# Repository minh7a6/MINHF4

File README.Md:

MINHF4 Hardware Design File. This board is designed using EAGLE 9.2.2

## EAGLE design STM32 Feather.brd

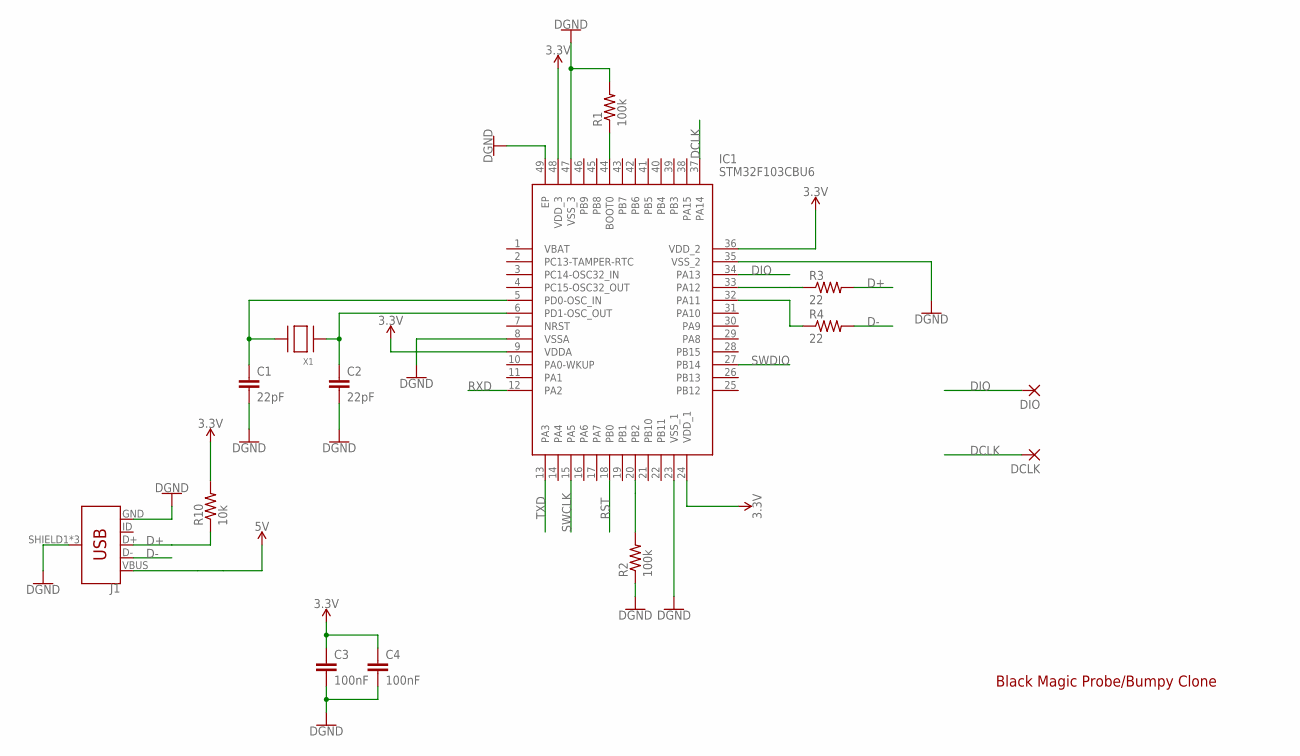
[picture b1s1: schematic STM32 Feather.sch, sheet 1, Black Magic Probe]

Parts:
C1, C2: 22pF; C0603
C3, C4: 100nF; C0603
DCLK: SMD2; SMD1,27-2,54
DIO: SMD2; SMD1,27-2,54
IC1: STM32F103CBU6; QFN50P700X700X65-49N
J1: USB_MICRO-B_FEMALE-SMT; USB-B-MICRO-SMD
R1, R2: 100k; R0603
R3, R4: 22; R0603
R10: 10k; R0603
X1: XTALNX5032; NX5032

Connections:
3.3V: C3.1, C4.1, IC1.9 (VDDA), IC1.24 (VDD_1), IC1.36 (VDD_2), IC1.48 (VDD_3), R10.2; also elsewhere on the board
5V: J1.VBUS; also elsewhere on the board
D+: J1.D+, R3.2, R10.1
D-: J1.D-, R4.2
DCLK: DCLK.1, IC1.37 (PA14)
DIO: DIO.1, IC1.34 (PA13)
GND: C1.2, C2.2, C3.2, C4.2, IC1.8 (VSSA), IC1.23 (VSS_1), IC1.35 (VSS_2), IC1.47 (VSS_3), IC1.49 (EP), J1.GND, J1.SHIELD1 (SHIELD), J1.SHIELD2 (SHIELD), J1.SHIELD3 (SHIELD), R1.2, R2.1; also elsewhere on the board
unnamed: C1.1, IC1.5 (PD0-OSC_IN), X1.P$2
unnamed: C2.1, IC1.6 (PD1-OSC_OUT), X1.P$1
unnamed: IC1.44 (BOOT0), R1.1
unnamed: IC1.20 (PB2), R2.2
unnamed: IC1.33 (PA12), R3.1
unnamed: IC1.32 (PA11), R4.1
RST: IC1.18 (PB0); also elsewhere on the board
RXD: IC1.12 (PA2); also elsewhere on the board
SWCLK: IC1.15 (PA5); also elsewhere on the board
SWDIO: IC1.27 (PB14); also elsewhere on the board
TXD: IC1.13 (PA3); also elsewhere on the board

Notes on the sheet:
Black Magic Probe/Bumpy Clone

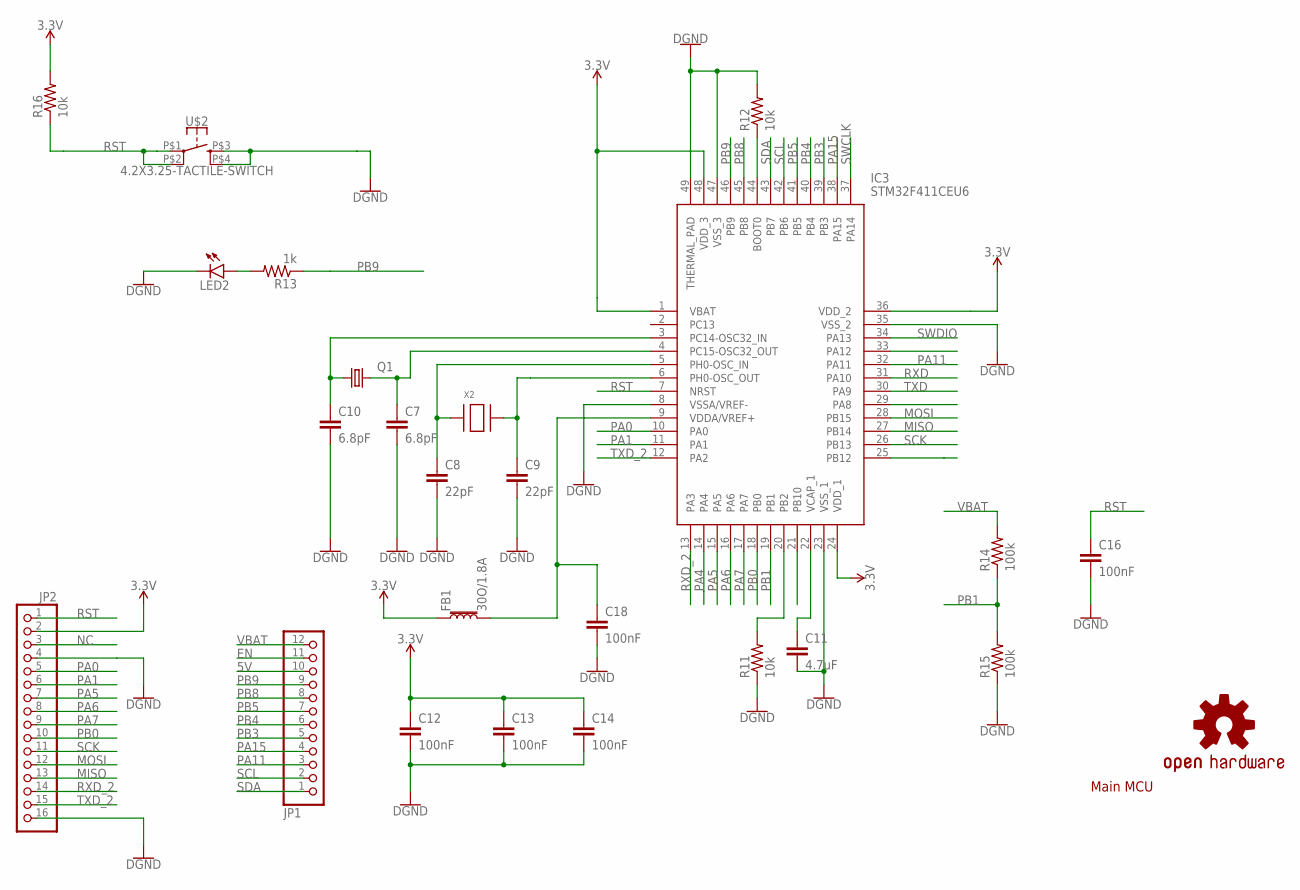
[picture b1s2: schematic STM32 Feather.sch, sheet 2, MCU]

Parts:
C7, C10: 6.8pF; C0603
C8, C9: 22pF; C0603
C11: 4.7uF; C0603
C12, C13, C14, C16, C18: 100nF; C0603
FB1: 30O/1.8A; 0603
IC3: STM32F411CEU6; QFN50P700X700X60-49N
JP1: PINHD-1X12; 1X12
JP2: PINHD-1X16; 1X16
LED2: LEDCHIP-LED0603; CHIP-LED0603
LOGO1: OSHW-LOGOMINI; OSHW-LOGO-MINI
Q1: KX-327-NHF; 3.2X1.5
R11, R12, R16: 10k; R0603
R13: 1k; R0603
R14, R15: 100k; R0603
U$2: 4.2X3.25-TACTILE-SWITCH; 4.2X3.25
X2: XTALNX5032; NX5032

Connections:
3.3V: C12.1, C13.1, C14.1, FB1.1, IC3.1 (VBAT), IC3.24 (VDD_1), IC3.36 (VDD_2), IC3.48 (VDD_3), JP2.2, R16.2; also elsewhere on the board
5V: JP1.10; also elsewhere on the board
EN: JP1.11
GND: C7.2, C8.2, C9.2, C10.2, C11.2, C12.2, C13.2, C14.2, C16.2, C18.2, IC3.8 (VSSA/VREF-), IC3.23 (VSS_1), IC3.35 (VSS_2), IC3.47 (VSS_3), IC3.49 (THERMAL_PAD), JP2.4, JP2.16, LED2.C, R11.1, R12.2, R15.1, U$2.P$3 (3), U$2.P$4 (4); also elsewhere on the board
MISO: IC3.27 (PB14), JP2.13
MOSI: IC3.28 (PB15), JP2.12
unnamed: LED2.A, R13.2
unnamed: C7.1, IC3.4 (PC15-OSC32_OUT), Q1.2
unnamed: C10.1, IC3.3 (PC14-OSC32_IN), Q1.1
unnamed: C18.1, FB1.2, IC3.9 (VDDA/VREF+)
unnamed: C8.1, IC3.5 (PH0-OSC_IN), X2.P$1
unnamed: C9.1, IC3.6 (PH0-OSC_OUT), X2.P$2
unnamed: C11.1, IC3.22 (VCAP_1)
unnamed: IC3.20 (PB2), R11.2
unnamed: IC3.44 (BOOT0), R12.1
NC: JP2.3
PA0: IC3.10 (PA0), JP2.5
PA1: IC3.11 (PA1), JP2.6
PA4: IC3.14 (PA4)
PA5: IC3.15 (PA5), JP2.7
PA6: IC3.16 (PA6), JP2.8
PA7: IC3.17 (PA7), JP2.9
PA11: IC3.32 (PA11), JP1.3
PA15: IC3.38 (PA15), JP1.4
PB0: IC3.18 (PB0), JP2.10
PB1: IC3.19 (PB1), R14.1, R15.2
PB3: IC3.39 (PB3), JP1.5
PB4: IC3.40 (PB4), JP1.6
PB5: IC3.41 (PB5), JP1.7
PB8: IC3.45 (PB8), JP1.8
PB9: IC3.46 (PB9), JP1.9, R13.1
RST: C16.1, IC3.7 (NRST), JP2.1, R16.1, U$2.P$1 (1), U$2.P$2 (2); also elsewhere on the board
RXD: IC3.31 (PA10); also elsewhere on the board
RXD_2: IC3.13 (PA3), JP2.14
SCK: IC3.26 (PB13), JP2.11
SCL: IC3.42 (PB6), JP1.2
SDA: IC3.43 (PB7), JP1.1
SWCLK: IC3.37 (PA14); also elsewhere on the board
SWDIO: IC3.34 (PA13); also elsewhere on the board
TXD: IC3.30 (PA9); also elsewhere on the board
TXD_2: IC3.12 (PA2), JP2.15
VBAT: JP1.12, R14.2; also elsewhere on the board

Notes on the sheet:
Main MCU

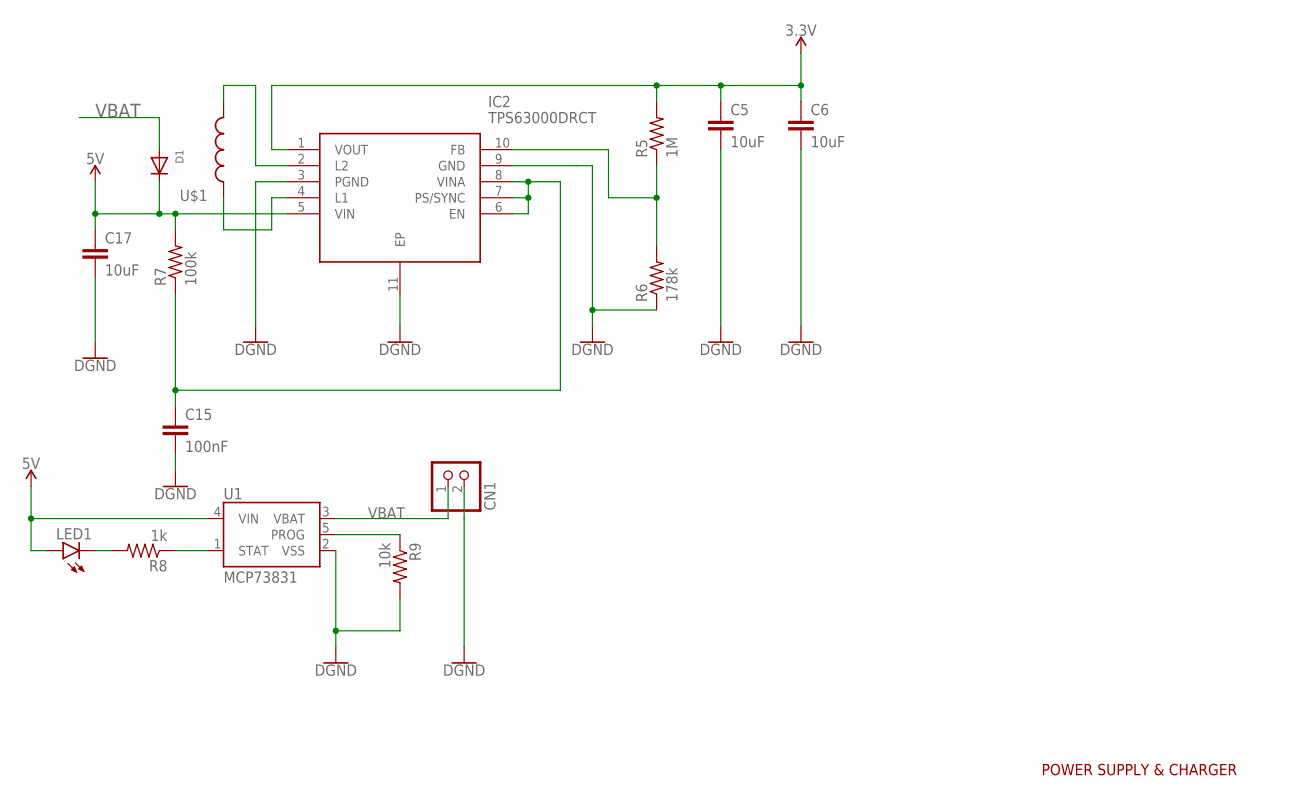
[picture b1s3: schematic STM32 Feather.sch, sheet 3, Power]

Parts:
C5: 10uF; C0805
C6, C17: 10uF; C0603
C15: 100nF; C0603
CN1: JST_2PIN-THM-RA; JST-PH-2-THM-RA
D1: DIODESOD-123; SOD-123
IC2: TPS63000DRCT; SON50P300X300X100-11N
LED1: LEDCHIPLED_0603; CHIPLED_0603
R5: 1M; R0603
R6: 178k; R0603
R7: 100k; R0603
R8: 1k; R0603
R9: 10k; R0603
U1: MCP73831; SOT23-5
U$1: SWPA252012S-INDUCTOR; SWPA25012S

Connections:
3.3V: C5.1, C6.1, IC2.1 (VOUT), R5.2; also elsewhere on the board
5V: C17.1, D1.C, IC2.5 (VIN), LED1.A, R7.2, U1.4 (VIN); also elsewhere on the board
GND: C5.2, C6.2, C15.2, C17.2, CN1.2 (1), IC2.3 (PGND), IC2.9 (GND), IC2.11 (EP), R6.1, R9.2, U1.2 (VSS); also elsewhere on the board
unnamed: C15.1, IC2.6 (EN), IC2.7 (PS/SYNC), IC2.8 (VINA), R7.1
unnamed: IC2.2 (L2), U$1.P$2 (2)
unnamed: IC2.4 (L1), U$1.P$1 (1)
unnamed: LED1.C, R8.2
unnamed: R8.1, U1.1 (STAT)
unnamed: R9.1, U1.5 (PROG)
unnamed: IC2.10 (FB), R5.1, R6.2
VBAT: CN1.1 (2), D1.A, U1.3 (VBAT); also elsewhere on the board

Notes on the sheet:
POWER SUPPLY & CHARGER

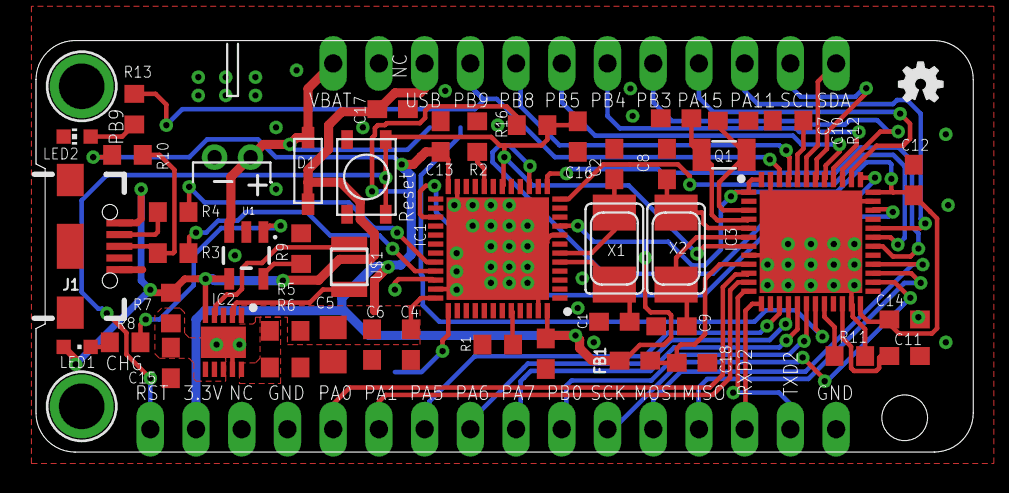
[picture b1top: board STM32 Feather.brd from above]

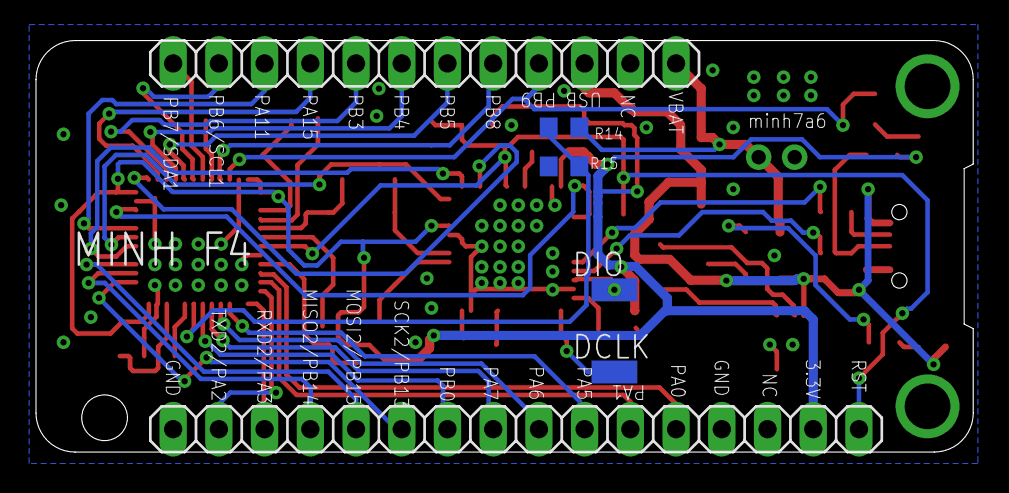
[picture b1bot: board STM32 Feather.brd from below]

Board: 2 copper layers, 52.1 x 22.9 mm, 54 parts (6 on the bottom side), 56 nets.

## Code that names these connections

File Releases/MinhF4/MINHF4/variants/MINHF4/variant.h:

/*
 *******************************************************************************
 * Copyright (c) 2017, STMicroelectronics
 * All rights reserved.
 *
 * Redistribution and use in source and binary forms, with or without
 * modification, are permitted provided that the following conditions are met:
 *
 * 1. Redistributions of source code must retain the above copyright notice,
 *    this list of conditions and the following disclaimer.
 * 2. Redistributions in binary form must reproduce the above copyright notice,
 *    this list of conditions and the following disclaimer in the documentation
 *    and/or other materials provided with the distribution.
 * 3. Neither the name of STMicroelectronics nor the names of its contributors
 *    may be used to endorse or promote products derived from this software
 *    without specific prior written permission.
 *
 * THIS SOFTWARE IS PROVIDED BY THE COPYRIGHT HOLDERS AND CONTRIBUTORS "AS IS"
 * AND ANY EXPRESS OR IMPLIED WARRANTIES, INCLUDING, BUT NOT LIMITED TO, THE
 * IMPLIED WARRANTIES OF MERCHANTABILITY AND FITNESS FOR A PARTICULAR PURPOSE ARE
 * DISCLAIMED. IN NO EVENT SHALL THE COPYRIGHT HOLDER OR CONTRIBUTORS BE LIABLE
 * FOR ANY DIRECT, INDIRECT, INCIDENTAL, SPECIAL, EXEMPLARY, OR CONSEQUENTIAL
 * DAMAGES (INCLUDING, BUT NOT LIMITED TO, PROCUREMENT OF SUBSTITUTE GOODS OR
 * SERVICES; LOSS OF USE, DATA, OR PROFITS; OR BUSINESS INTERRUPTION) HOWEVER
 * CAUSED AND ON ANY THEORY OF LIABILITY, WHETHER IN CONTRACT, STRICT LIABILITY,
 * OR TORT (INCLUDING NEGLIGENCE OR OTHERWISE) ARISING IN ANY WAY OUT OF THE USE
 * OF THIS SOFTWARE, EVEN IF ADVISED OF THE POSSIBILITY OF SUCH DAMAGE.
 *******************************************************************************
 */

#ifndef _VARIANT_ARDUINO_STM32_
#define _VARIANT_ARDUINO_STM32_

/*----------------------------------------------------------------------------
 *        Headers
 *----------------------------------------------------------------------------*/
#include "PeripheralPins.h"

#ifdef __cplusplus
extern "C"{
#endif // __cplusplus

/*----------------------------------------------------------------------------
 *        Pins
 *----------------------------------------------------------------------------*/
extern const PinName digitalPin[];
 #define PA3 0 //D0/TXD2
 #define PA2 1 //D1/RXD2
 #define PA9 2 //D2
 #define PA10 3 //D3
 #define PA12 4 //D4
 #define PA11 5 //D5
 #define PA15 6 //D6
 #define PA4 7 //D7
 #define PB2 8 //D8
 #define PB3 9 //D9
 #define PB4 10 //D10
 #define PB5 11 //D11
 #define PB8 12 //D12
 #define PB9 13 //D13
 #define PB7 14 //D14
 #define PB6 15 //D15
 #define PB15 16 //D16
 #define PB14 17 //D17
 #define PB13 18 //D18
 #define PB12 19 //D19
 #define PB11 20 //D20
 #define PA8 21 //D21
 #define PA13 22 //D22
 #define PA14 23 //D23
 #define PC13 24 //D24
 #define PC14 25 //D25
 #define PC15 26 //D26
 #define PA0 27 //D27
 #define PA1 28 //D28
 #define PA5 29 //D29
 #define PA6 30 //D30
 #define PA7 31 //D31
 #define PB0 32 //D32
 #define PB1 33 //D33
// Define pin names to match digital pin number --> Dx
// It could be used with preprocessor tests (e.g. #if PXn == 3)
// so an enum will not work.
// !!!
// !!! Copy the digitalPin[] array from the variant.cpp
// !!! and remove all '_': PX_n --> PXn
// !!! For NC, comment the line to warn x pin number is NC
// !!! // x is NC
// !!! For duplicated pin name, comment the line to warn x pin number
// !!! is PXn which is already defined with y pin number
// !!! // x is PXn (y)
// !!! Ex:
// !!! ...
// !!! #define PA4  20 // A14
// !!! #define PB4  21
// !!! #define PB5  22
// !!! #define PB3  23
// !!! // 24 is PA4 (20)
// !!! // 25 is PB4 (21)// #define PXn x
// !!! #define PA2  26 // A15
// !!! ...
//#define PXn x

// This must be a literal
// It is used with preprocessor tests (e.g. #if NUM_DIGITAL_PINS > 3)
// so an enum will not work.
#define NUM_DIGITAL_PINS        37

// Allow to define Arduino style alias for analog input pin number --> Ax
// All pins are digital, analog inputs are a subset of digital pins
// and must be contiguous to be able to loop on each value
// This must be a literal with a value less than or equal to MAX_ANALOG_INPUTS
// defined in pin_arduino.h
// It is used with preprocessor tests (e.g. #if NUM_ANALOG_INPUTS > 3)
// so an enum will not work.
// !!!
// !!! It must be aligned with the number of analog PinName
// !!! defined in digitalPin[] array in variant.cpp
// !!!
#define NUM_ANALOG_INPUTS       10
// Define digital pin number of the first analog input  (i.e. which digital pin is A0)
// First analog pin value (A0) must be greater than or equal to NUM_ANALOG_INPUTS
#define NUM_ANALOG_FIRST        27

// Below ADC, DAC and PWM definitions already done in the core
// Could be redefined here if needed
// ADC resolution is 12bits
//#define ADC_RESOLUTION          12
//#define DACC_RESOLUTION         12

// PWM resolution
//#define PWM_RESOLUTION          8
//#define PWM_FREQUENCY           1000
//#define PWM_MAX_DUTY_CYCLE      255

// On-board LED pin number
#define LED_BUILTIN             13
#define LED_GREEN               LED_BUILTIN

// On-board user button
//#define USER_BTN                x

// Below SPI and I2C definitions already done in the core
// Could be redefined here if differs from the default one
// SPI Definitions
//#define PIN_SPI_SS              10 // Default for Arduino connector compatibility
//#define PIN_SPI_MOSI            11 // Default for Arduino connector compatibility
//#define PIN_SPI_MISO            12 // Default for Arduino connector compatibility
//#define PIN_SPI_SCK             13 // Default for Arduino connector compatibility

// I2C Definitions
//#define PIN_WIRE_SDA            14 // Default for Arduino connector compatibility
//#define PIN_WIRE_SCL            15 // Default for Arduino connector compatibility

// Timer Definitions
//Do not use timer used by PWM pins when possible. See PinMap_PWM in PeripheralPins.c
#define TIMER_TONE              TIM10

// Do not use basic timer: OC is required
#define TIMER_SERVO             TIM2  //TODO: advanced-control timers don't work

// UART Definitions
// Define here Serial instance number to map on Serial generic name
#define SERIAL_UART_INSTANCE    1 //ex: 2 for Serial2 (USART2)
// DEBUG_UART could be redefined to print on another instance than 'Serial'
//#define DEBUG_UART              ((USART_TypeDef *) U(S)ARTX) // ex: USART3
// DEBUG_UART baudrate, default: 9600 if not defined
//#define DEBUG_UART_BAUDRATE     x
// DEBUG_UART Tx pin name, default: the first one found in PinMap_UART_TX for DEBUG_UART
//#define DEBUG_PINNAME_TX        PX_n // PinName used for TX

// Default pin used for 'Serial' instance (ex: ST-Link)
// Mandatory for Firmata
#define PIN_SERIAL_RX           PA10
#define PIN_SERIAL_TX           PA9

// Optional PIN_SERIALn_RX and PIN_SERIALn_TX where 'n' is the U(S)ART number
// Used when user instanciate a hardware Serial using its peripheral name.
// Example: HardwareSerial mySerial(USART3);
// will use PIN_SERIAL3_RX and PIN_SERIAL3_TX if defined.
#define PIN_SERIAL2_RX          PA3 // For U(S)ARTn RX
#define PIN_SERIAL2_TX          PA2 // For U(S)ARTn TX
//#define PIN_SERIALLP1_RX        x // For LPUART1 RX
//#define PIN_SERIALLP1_TX        x // For LPUART1 TX

// SD card slot Definitions
// SD detect signal can be defined if required
//#define SD_DETECT_PIN           x
// SD Read/Write timeout, default value defined in STM32SD library
//#define SD_DATATIMEOUT          x

#ifdef __cplusplus
} // extern "C"
#endif
/*----------------------------------------------------------------------------
 *        Arduino objects - C++ only
 *----------------------------------------------------------------------------*/

#ifdef __cplusplus
// These serial port names are intended to allow libraries and architecture-neutral
// sketches to automatically default to the correct port name for a particular type
// of use.  For example, a GPS module would normally connect to SERIAL_PORT_HARDWARE_OPEN,
// the first hardware serial port whose RX/TX pins are not dedicated to another use.
//
// SERIAL_PORT_MONITOR        Port which normally prints to the Arduino Serial Monitor
//
// SERIAL_PORT_USBVIRTUAL     Port which is USB virtual serial
//
// SERIAL_PORT_LINUXBRIDGE    Port which connects to a Linux system via Bridge library
//
// SERIAL_PORT_HARDWARE       Hardware serial port, physical RX & TX pins.
//
// SERIAL_PORT_HARDWARE_OPEN  Hardware serial ports which are open for use.  Their RX & TX
//                            pins are NOT connected to anything by default.
#define SERIAL_PORT_MONITOR     Serial
#define SERIAL_PORT_HARDWARE    Serial
#endif

#endif /* _VARIANT_ARDUINO_STM32_ */

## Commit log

2019-02-11 First Push
2019-02-11 fixes
2019-02-11 First Push for MINHF4 Design
2019-02-11 Changes on the format
2019-02-11 changes in pdf file
2019-02-11 added picture
2019-02-14 insert JSON
2019-02-14 fix json
2019-02-14 fixes bugs
2019-02-14 fixes json files
2019-02-14 fix bugs
2019-02-14 raw files for manual installation

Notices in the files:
parts and their libraries:
SparkFun-Connectors: Licensing: Creative Commons ShareAlike 4.0 International - https://creativecommons.org/licenses/by-sa/4.0
crystal-geyer_V1_0: Copyright: Geyer-Electronic
